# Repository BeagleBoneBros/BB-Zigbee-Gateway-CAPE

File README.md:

# Readme
- Purpose: The purpose of this project is to provide the Seeed Studio Beagle Bone Green Gateway with the ability to communicate via Zigbee through the means of a custom PCB that connects to the GPIO headers of the BeagleBone. In addition to providing the BeagleBone with the ability to communicate with a new protocol, it will also be able to host a MQTT Broker server that can be used to establish topics for smart devices such as lightbulbs, switches, and sensors. The Github for the MQTT Gateway Software can be found at the Github link below.

- Structure: This repository is designed and structured to be downloaded to a local machine such that the user can open the single "BeagleBone-Black-Cape.pro" file. All user-created footprints and symbols are included in this repository and are mapped relative to the .pro file.

- Created by: Tyler Beach, Zachary Wells, Adam Hood

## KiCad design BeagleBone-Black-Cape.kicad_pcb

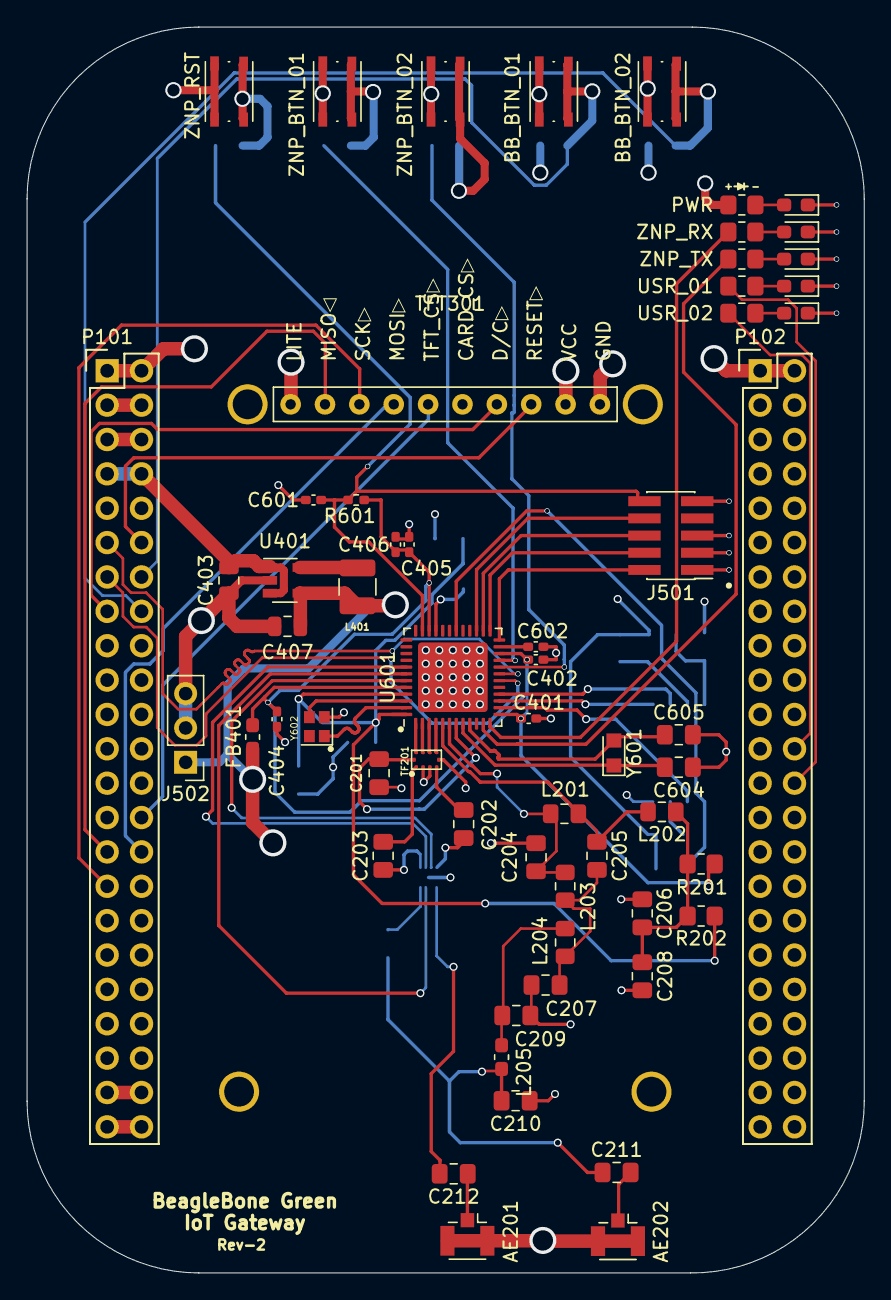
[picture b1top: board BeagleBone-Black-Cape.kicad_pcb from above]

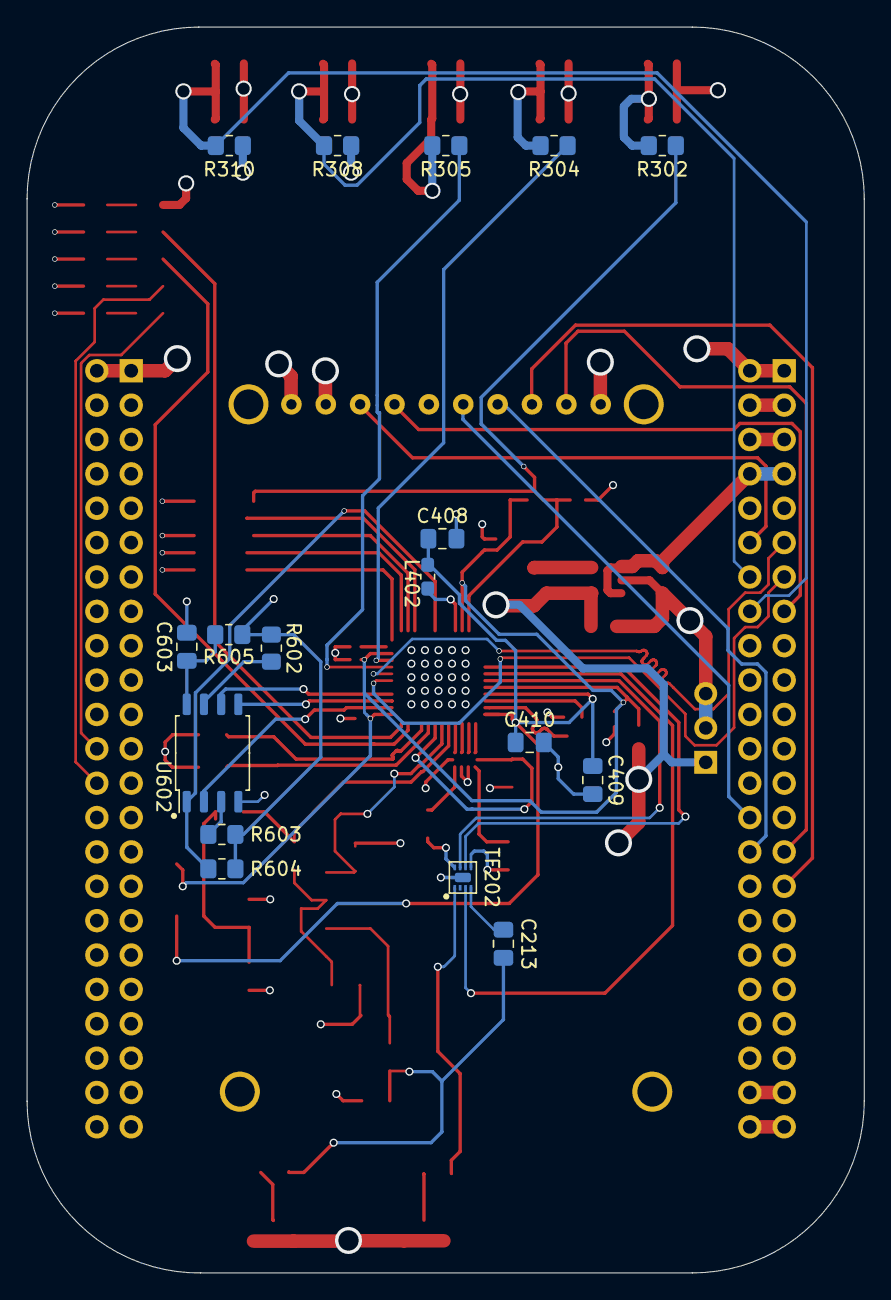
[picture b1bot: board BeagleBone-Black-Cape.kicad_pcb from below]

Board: 4 copper layers, 61.9 x 92.1 mm, 77 parts (17 on the bottom side), 72 nets.

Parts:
AE201, AE202: 50Ω; U.FL_Hirose_U.FL-R-SMT-1_Vertical
BB_BTN_01, BB_BTN_02: SW_Push; SW_Push_1P1T_NO_Vertical_Wuerth_434133025816
C201, C202: 100pF; C_0805_2012Metric_Pad1.18x1.45mm_HandSolder
C203, C213: 47pF; C_0805_2012Metric_Pad1.18x1.45mm_HandSolder
C204, C205: 1.2pF; C_0805_2012Metric_Pad1.18x1.45mm_HandSolder
C206: 12pF; C_0805_2012Metric_Pad1.18x1.45mm_HandSolder
C207: 2.7pF; C_0805_2012Metric_Pad1.18x1.45mm_HandSolder
C208: 10nF; C_0805_2012Metric_Pad1.18x1.45mm_HandSolder
C209: 1.8pF; C_0805_2012Metric_Pad1.18x1.45mm_HandSolder
C210: 1.5pF; C_0805_2012Metric_Pad1.18x1.45mm_HandSolder
C211, C212: DNF; C_0805_2012Metric_Pad1.18x1.45mm_HandSolder
C401, C402, C404, C406, C601: 0.1u; C_0402_1005Metric_Pad0.74x0.62mm_HandSolder
C403: 4.7uF; C_0805_2012Metric
C405: 22u; C_0402_1005Metric_Pad0.74x0.62mm_HandSolder
C407: 10uF; C_0805_2012Metric
C408: 22u; C_0805_2012Metric_Pad1.18x1.45mm_HandSolder
C409, C410, C603: 0.1u; C_0805_2012Metric_Pad1.18x1.45mm_HandSolder
C602: 1u; C_0402_1005Metric_Pad0.74x0.62mm_HandSolder
C604, C605: CAP; C_0805_2012Metric_Pad1.18x1.45mm_HandSolder
FB401: 1500 Ohm 500mA; L_0603_1608Metric_Pad1.05x0.95mm_HandSolder
J501: Conn_ARM_JTAG_SWD_10; PinHeader_2x05_P1.27mm_Vertical_SMD
J502: 3.3V; PinHeader_1x03_P2.54mm_Vertical
L201: 15nH; L_0805_2012Metric_Pad1.15x1.40mm_HandSolder
L202, L203: 3nH; L_0805_2012Metric_Pad1.15x1.40mm_HandSolder
L204: 1.8nH; L_0805_2012Metric_Pad1.15x1.40mm_HandSolder
L205: 1nH; L_0603_1608Metric_Pad1.05x0.95mm_HandSolder
L401: 2.2uH; L_1210_3225Metric
L402: 6.8u; L_0603_1608Metric_Pad1.05x0.95mm_HandSolder
P101, P102: BeagleBone_Black_Header; Socket_BeagleBone_Black
PWR: LED; LED_0603_1608Metric_Pad1.05x0.95mm_HandSolder
R201, R605: 0; R_0805_2012Metric_Pad1.20x1.40mm_HandSolder
R202: DNF; R_0805_2012Metric_Pad1.20x1.40mm_HandSolder
R301, R303, R306, R307, R309: R_US; R_0805_2012Metric_Pad1.20x1.40mm_HandSolder
R302, R304, R305: 100; R_0805_2012Metric_Pad1.20x1.40mm_HandSolder
R308, R310: 100k; R_0805_2012Metric_Pad1.20x1.40mm_HandSolder
R601: 100k; R_0402_1005Metric_Pad0.72x0.64mm_HandSolder
R602, R603: DNS; R_0805_2012Metric_Pad1.20x1.40mm_HandSolder
R604: 2.2k; R_0805_2012Metric_Pad1.20x1.40mm_HandSolder
TF201: IPC_1352P
TF202: SKY13317-373; SKY13317-373LF-BH
TFT301: ST7735_TFT; ST7735
U401: LM3671; SOT-23-5
U601: cc1352p; VQFN-48-1EP_7x7mm_P0.5mm_EP5.15x5.15mm
U602: MX25R8035FZUIL0; SOP-8_5.28x5.23mm_P1.27mm
USR_01, USR_02: LED; LED_0603_1608Metric_Pad1.05x0.95mm_HandSolder
Y601: 32.768kHz; Crystal_SMD_2012-2Pin_2.0x1.2mm_HandSoldering
Y602: 48MHz; Crystal_SMD_2016-4Pin_2.0x1.6mm
ZNP_BTN_01, ZNP_BTN_02: SW_Push; SW_Push_1P1T_NO_Vertical_Wuerth_434133025816
ZNP_RST: 612-LL3303F065QG; SW_Push_1P1T_NO_Vertical_Wuerth_434133025816
ZNP_RX: LED; LED_0603_1608Metric_Pad1.05x0.95mm_HandSolder
ZNP_TX: LED; LED_0603_1608Metric_Pad1.05x0.95mm_HandSolder

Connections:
2.4N: TF201.8, U601.2
2.4P: TF201.9, U601.1
+3V3: P101.3, P101.4
+5V: P101.5, P101.6
BB_BTN_1: BB_BTN_01.2, P101.14, R308.1
BB_BTN_2: BB_BTN_02.2, P101.16, R310.1
BB_LED_1: P102.24, R307.1
BB_LED_2: P102.26, R309.1
CS_TFT: P101.28, TFT301.5
D.C_TFT: P101.15, TFT301.7
DCDC_SW: L402.1, U601.33
GND: AE201.2, AE202.2, BB_BTN_01.1, BB_BTN_02.1, C201.1, C204.1, C206.2, C207.2, C208.2, C209.2, C210.2, C401.2, C402.2, C403.2, C404.2, C405.2, C406.2, C407.2, C408.2, C409.2, C410.2, C601.2, C602.2, C603.2, C604.2, C605.2, J501.3, J501.5, J501.9, J502.2, J502.3, P101.1, P101.2, P101.43, P101.44, P101.45, P101.46, P102.1, P102.2, PWR.1, TF201.2, TF201.3, TF201.10, TF202.9, TFT301.10, U401.2, U601.49, U602.4, USR_01.1, USR_02.1, Y602.2, ZNP_BTN_01.1, ZNP_BTN_02.1, ZNP_RST.1, ZNP_RX.1, ZNP_TX.1
MCU_BTN_1: R304.2, U601.21
MCU_BTN_2: R305.2, U601.20
MCU_LED_1: R303.1, U601.12
MCU_LED_2: R306.1, U601.11
MCU_RESET: C601.1, J501.10, R302.2, R601.1, U601.35
MCU_TCK: J501.4, U601.25
MCU_TDI: J501.8, U601.27
MCU_TDO: J501.6, U601.26
MCU_TMS: J501.2, U601.24
MCU_VDD: C407.1, FB401.2, J501.1, J502.1, L401.2, R301.1, R308.2, R310.2, R602.1, R603.1, R604.1, R605.1, TFT301.1, TFT301.9, U401.4
MISO_TFT: P101.29, TFT301.2
MOSI_TFT: P101.30, TFT301.4
unnamed: AE201.1, C212.1
unnamed: AE202.1, C211.2
unnamed: R307.2, USR_02.2
unnamed: R309.2, USR_01.2
unnamed: C202.1, TF202.5
unnamed: C202.2, TF201.4
unnamed: C203.1, TF202.8
unnamed: C203.2, TF201.1
unnamed: C205.2, C207.1, L203.2, L204.1
unnamed: C206.1, C208.1, L202.1, R201.2, R202.2
unnamed: C209.1, L204.2, L205.1
unnamed: C210.1, C211.1, C213.1, L205.2
unnamed: C212.2, TF202.1
unnamed: C602.1, U601.23
unnamed: C603.1, R605.2, U602.8
unnamed: L401.1, U401.5
unnamed: R303.2, ZNP_RX.2
unnamed: R306.2, ZNP_TX.2
unnamed: PWR.2, R301.2
unnamed: R302.1, ZNP_RST.2
unnamed: R304.1, ZNP_BTN_01.2
unnamed: R305.1, ZNP_BTN_02.2
unnamed: R602.2, U602.7
unnamed: R603.2, U602.3
unnamed: R604.2, U601.30, U602.1
unnamed: U601.14, U602.2
unnamed: U601.15, U602.5
unnamed: U601.16, U602.6
RST_TFT: P101.12, TFT301.8
RX_TX: C201.2, TF201.5, U601.7
SCK_TFT: P101.31, TFT301.3
SKY_RF1_20dBm: C213.2, TF202.4
SKY_V1_20DBM: TF202.3, U601.42
SKY_V2_SUB1G: TF202.6, U601.43
SKY_V3_2G4: TF202.7, U601.41
SUB1N: TF201.6, U601.4
SUB1P: TF201.7, U601.3
SYS_5V: C403.1, P101.7, P101.8, U401.1, U401.3
TX_20dB_N: C204.2, L201.2, L203.1, U601.6
TX_20dB_P: C205.1, L201.1, L202.2, U601.5
VDDR: C408.1, C409.1, C410.1, L402.2, R202.1, U601.45, U601.48
VDDS: C401.1, C402.1, C404.1, C405.1, C406.1, FB401.1, R201.1, R601.2, U601.13, U601.22, U601.34, U601.44
X32K_Q1: C604.1, U601.8, Y601.1
X32K_Q2: C605.1, U601.9, Y601.2
X48M_N: U601.46, Y602.3
X48M_P: U601.47, Y602.1
ZNP_RX: P101.13, U601.18
ZNP_TX: P101.11, U601.19

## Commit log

2021-02-23 fixed library for cc1352.lib
2021-02-23 fixed library
2021-02-23 finished cc1352 part
2021-02-23 Added readme
2021-02-23 added test txt file
2021-02-23 deleted txt file
2021-02-23 fixed 1352 part, finished differential circuit
2021-02-24 did more work on the schematic
2021-03-13 Finished schematic and PCB design for 2.4GHz and Sub 1GHz
2021-04-02 Added new symbols and footprints | Updated schematic for RF
2021-04-03 Part way through rats nest of 20dB branch and RF switcher
2021-08-02 Just a summer update to make sure we're all on the same page
2021-08-07 test commit
2021-08-07 Added footprint for TR05S3V3
2021-08-07 Drew up schematic for power subsystem
2021-08-07 Moved the footprint to be kinda centered at the orgin
2021-08-07 Updated refs and values for components
2021-08-24 Added PSU_ prepend to PSU specific global labels in the schematic
2021-09-07 Fixed "alias not found" warning
2021-09-07 added crystal oscillator circuit
2021-09-09 straightened out traces going to MCU (lines 1-7)
2021-09-09 Realigned some crooked traces on the PCB. Updated footprints for the PSU and associated components on behalf of Zach.
2021-09-11 Replaced old PSU circuit with the new one
2021-09-15 Added footprints and datasheets for oscillators
2021-09-16 Created footprint and assigned it
2021-09-17 PSU footprint validation done. Also updated reference values for L and C for that subsystem.
2021-09-19 Added Buttons, LEDs and MCU to BB connections.
2021-09-19 Fixed error with antenna system modification.
2021-09-20 Corrected RX/TX Connections to BB.
2021-09-20 Added Some Values
2021-09-21 Added JTAG to sch.
2021-09-21 Debug subsystem added
2021-09-21 i'm about to say fuck it to the pcb. if it doesn't work out. return here
2021-09-21 computer sync. part way through footprint
2021-09-21 finished IPC footprint and symbol
2021-09-21 implementation of IPC and SDPT IC's are done. Still need to sort +20dBm branch
2021-09-22 part way through getting new ICs and other components back on the PCB
2021-09-22 finished footprint for new switcher IC
2021-09-22 fixed the 20dBm branch and switched back to the 3 port band switcher IC
2021-09-22 Added UI buttons, LEDs, Decoupling caps, MCU connections, and other good stuff.
2021-09-22 Moved MCU to its own sheet.
2021-09-22 Finished Adding MCU connections and combined crystal and MCU sheets.
2021-09-22 Fixed some Global labels.
2021-09-22 Added Footprints for UI, JTAG, and some power stuff.
2021-09-22 part way through PCB rework using new components. 62 unconnected.
2021-09-23 Connected psup components together
2021-09-24 finished RF side of schematic. We need ground planes and Xtals
2021-09-24 Added Flash IC and PB/LED footprints.
2021-09-25 Revert "Added Flash IC and PB/LED footprints."
2021-09-27 FOUR LAYER BOARD CHANGE. We still need to adapt the other subsystems for four layers
2021-09-28 slowly but surely getting more things connected. trying to merge UI footprints. Standby
2021-09-28 This is a new commit.
2021-09-28 relinked LED and BTN footprints. Need to make flash symbol again
2021-09-28 Recovered the .lib for flash symbol. Relinked in schematic
2021-09-28 more library nonsense
2021-09-28 prepped for PSU subsystem placements
2021-09-28 Connected PSUP, track lengths fixed for xtals
    PSUP has been connected to power and ground planes. Traces have been made larger for that. The trace lengths have been matched for the xtals so that they should have the same properties.
2021-09-28 MOST CURRENT. NEED TO PLACE MORE STUFF
2021-09-29 Centered TFT display on the board
    Centered the TFT display on the board. The footprint was modified so the origin was the center of the component.
2021-09-29 Added more connections and other changes
2021-09-29 slow and steady wins the race. Zach read the ZACH READ ME.txt
2021-10-01 SCREW THIS. I'M SICK OF IT
2021-10-02 sync push so zach can work
2021-10-10 accepted Tyler's stuff, Auto stash before merge of "PCB-CATCHUP-TBEACH" and "origin/PCB-CATCHUP-TBEACH"
2021-10-11 Added more connections
    Connections added for the Push buttons, JTAG header, and LEDs
2021-10-11 ?
    I don't know why these are in here or being tracked
2021-10-11 Massive PCB/Schematic Update
    The PCB has been completed, and the schematic has been updated to have the correct footprints
2021-10-11 tyler once over. found two resistors that were missing traces. fixed.
2021-10-11 Zach once over, resized some components, connected VDDS pins
2021-10-11 Fixed Schematic connection issue and routed some missing traces.
2021-11-06 via conversion complete
2021-11-06 filling around new through vias complete. need reviews. onto zach for LCD holes and index dots
2021-11-07 updated footprint, updated some traces, added indexing dots
2021-11-07 added silkscreen with board name and revision number
2021-11-07 Fixed U601 p19 being connected to GND net instead of ZNP_TX
2021-11-07 Connected U.FL ground pins to ground and 2x23 connector ground pins to each other
2021-11-07 Used PCB cleanup tool w/o the "delete track segments connecting different nets" option (it keeps unlisted pins happy)
2021-11-07 Updated schematic and a symbol so that Y602 pad 4 was connected to the gnd net
2021-11-07 Made ZNP_RX trace prettier
2021-11-07 undid the Y602 Pad thing after crossreferencing datasheet
2021-11-07 Fixed silkscreens for buttons and LEDs
2021-11-07 Apparently the schematic wasn't saved, and thus not commited. Here's that commit.
2021-11-08 resolved DRC issues. Tyler check done. Awaiting 2/3 checks
2021-11-09 Went over things with Smoak again. Small revisions
2021-12-02 Last minute fixes before staging for public
2021-12-02 lib update so it only includes user-made library
2021-12-02 clean up crew on aisle 11
2021-12-02 no message
2021-12-04 final edits before it'll be untouched
